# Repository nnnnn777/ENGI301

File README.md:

# EZ Cool 1.0

This device was created to automate a Lasko brand box fan, or other similar box fans, by using the PocketBeagle.

## Table of Contents

- [Features](#features)
- [Set Up](#setup)
- [Usage](#usage)

## Features

This device features LEDs, buttons, and a servo motor. Bluetooth integration will be added in the future.

## Set Up
Instructions on device build and set up can be found at the following Hackster page: [Hackster](https://www.hackster.io/511889/ez-cool-1-0-pocketbeagle-5790c5)

## Usage

This device operates on its own once connected to power. Simply plug in EZ Cool 1.0 after attaching to the fan and wait for the red LED to power on.

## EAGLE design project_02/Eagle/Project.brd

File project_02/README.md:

# ENGI 301: Project 2/EZ Cool

This folder contains files pertaining to the electronic components of the EZ Cool PocketBeagle based device by Nate Miller including .sch, .brd, .lib, and some other miscellaneous files.
For more on this device, please see project_1.

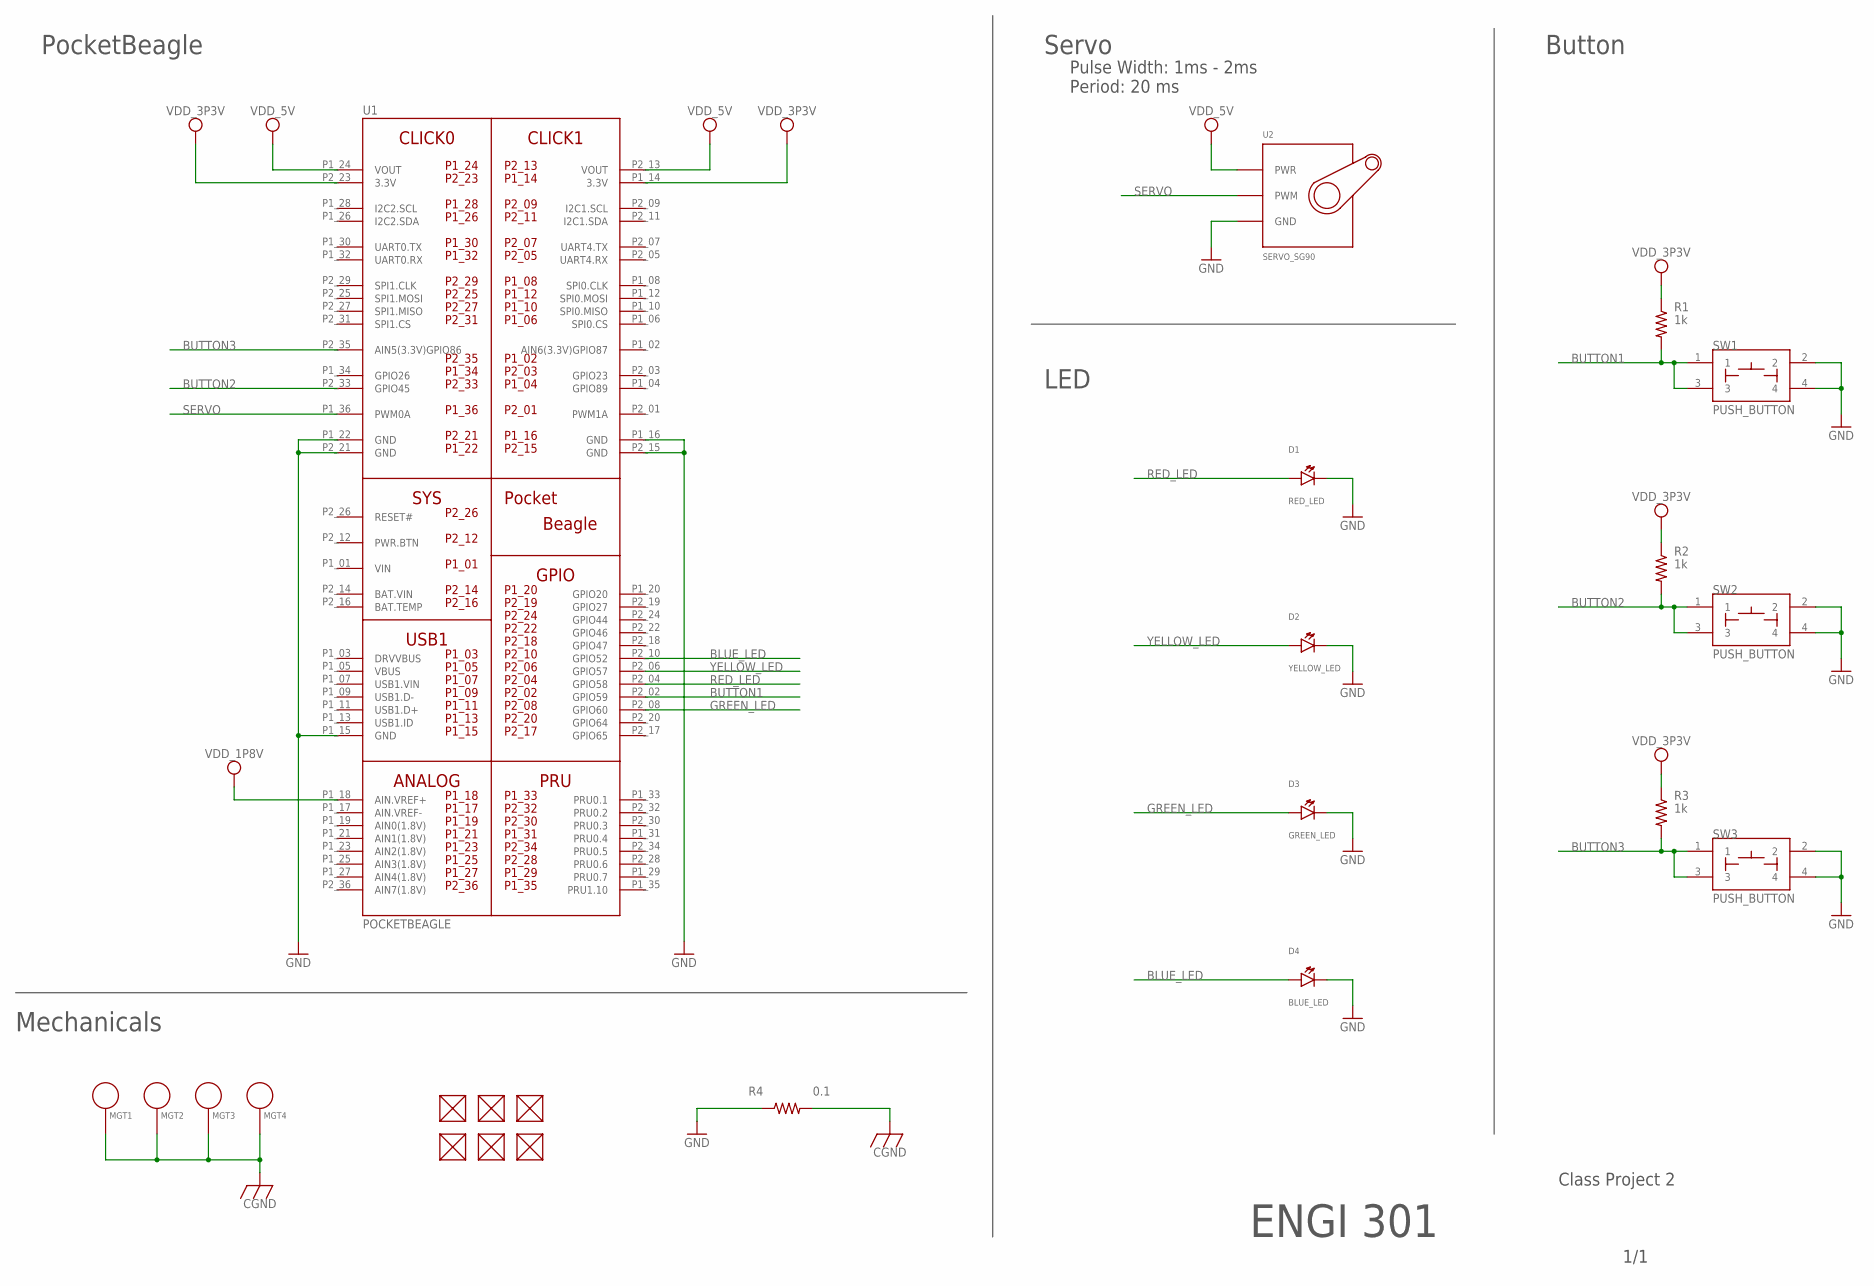
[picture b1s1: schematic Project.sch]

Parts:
D1: RED_LED; EIA-STD
D2: YELLOW_LED; EIA-STD
D3: GREEN_LED; EIA-STD
D4: BLUE_LED; EIA-STD
FUD1, FUD2, FUD3, FUD4, FUD5, FUD6: FIDUCIAL; FIDUCIAL_40MIL
MGT1, MGT2, MGT3, MGT4: MOUNTING_HOLE
R1, R2, R3: 1k; R0603
R4: 0.1; R0805
SW1, SW2, SW3: PUSH_BUTTON; BUTTON_12.5MM
U1: POCKETBEAGLE
U2: SERVO_SG90; SERVO-X1

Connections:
BAT.VIN: U1.P2_14 (BAT.VIN)
BLUE_LED: D4.ANODE, U1.P2_10 (GPIO52)
BUTTON1: R1.2, SW1.1, SW1.3, U1.P2_02 (GPIO59)
BUTTON2: R2.2, SW2.1, SW2.3, U1.P2_33 (GPIO45)
BUTTON3: R3.2, SW3.1, SW3.3, U1.P2_35 (AIN5(3.3V)GPIO86)
CGND: MGT1.P$1, MGT2.P$1, MGT3.P$1, MGT4.P$1, R4.2
GND: D1.CATHODE, D2.CATHODE, D3.CATHODE, D4.CATHODE, R4.1, SW1.2, SW1.4, SW2.2, SW2.4, SW3.2, SW3.4, U1.P1_15 (GND), U1.P1_16 (GND), U1.P1_22 (GND), U1.P2_15 (GND), U1.P2_21 (GND), U2.GND
GREEN_LED: D3.ANODE, U1.P2_08 (GPIO60)
RED_LED: D1.ANODE, U1.P2_04 (GPIO58)
SERVO: U1.P1_36 (PWM0A), U2.SIG (PWM)
VDD_1P8V: U1.P1_18 (AIN.VREF+)
VDD_3P3V: R1.1, R2.1, R3.1, U1.P1_14 (3.3V), U1.P2_23 (3.3V)
VDD_5V: U1.P1_24 (VOUT), U1.P2_13 (VOUT), U2.PWR
VIN: U1.P1_01 (VIN)
YELLOW_LED: D2.ANODE, U1.P2_06 (GPIO57)

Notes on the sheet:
PocketBeagle
Servo
Button
LED
Pulse Width: 1ms - 2ms Period: 20 ms
Mechanicals
Class Project 2
1/1
ENGI 301

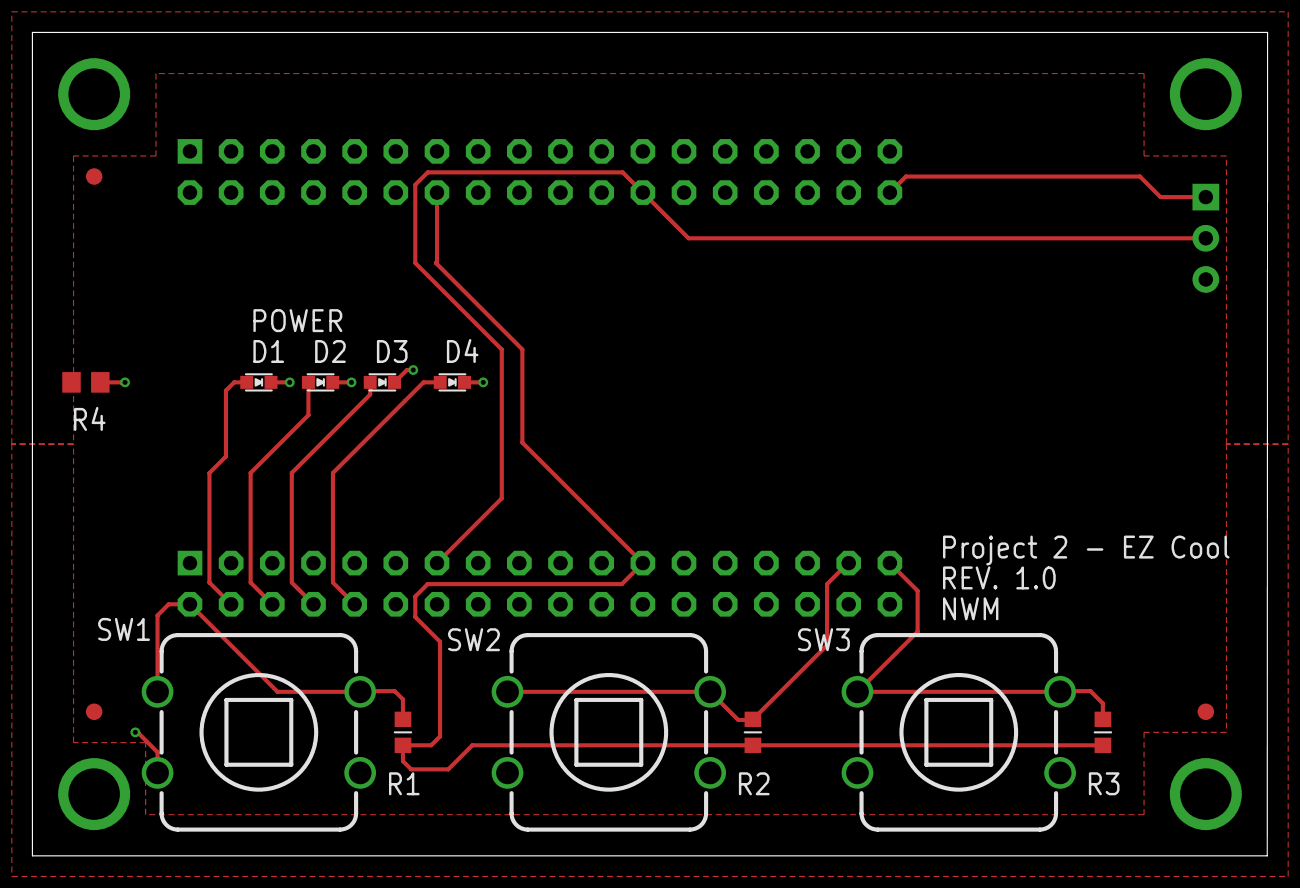
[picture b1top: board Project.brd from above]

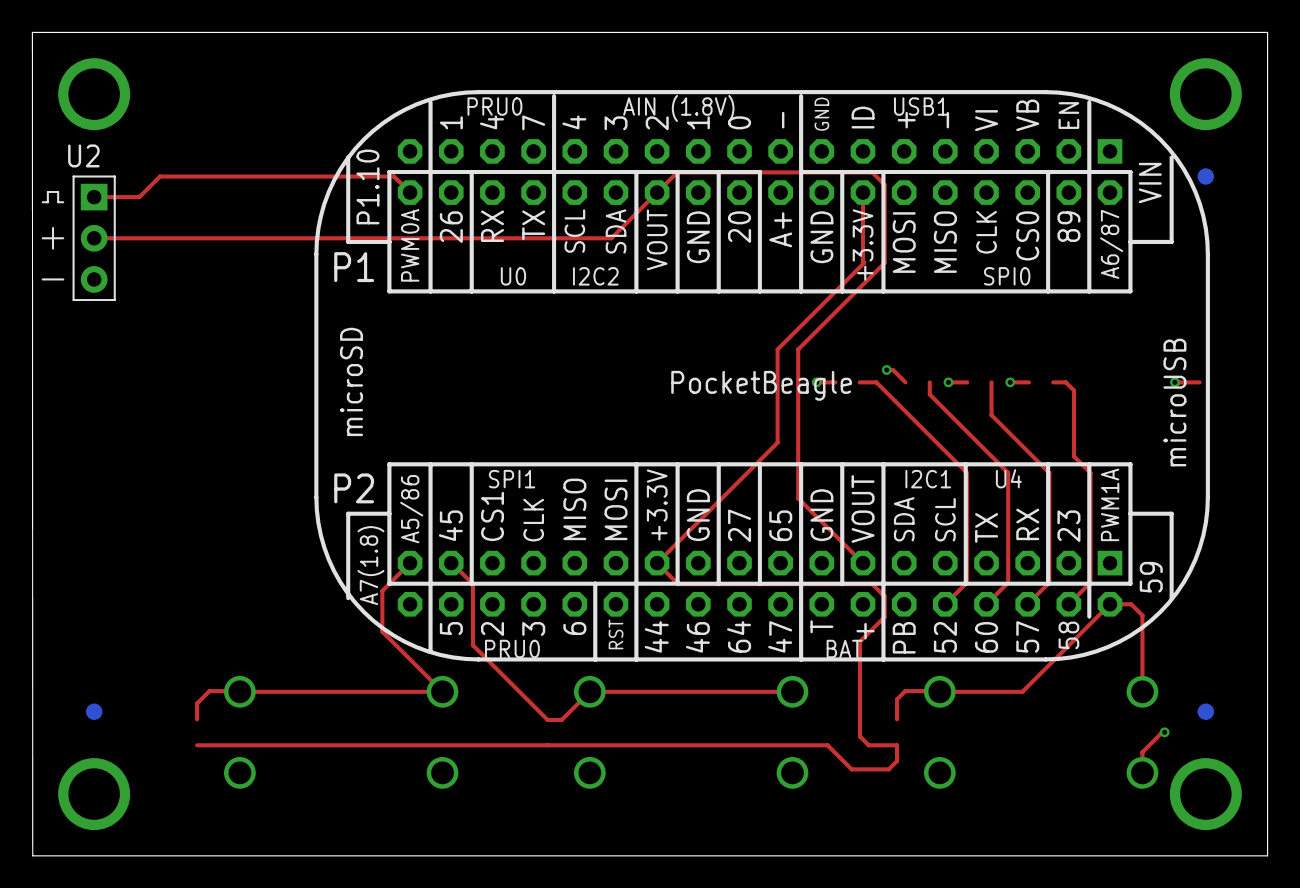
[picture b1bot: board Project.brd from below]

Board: 4 copper layers, 76.2 x 50.8 mm, 23 parts (5 on the bottom side), 12 nets.

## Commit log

2023-09-13 Updating README.md
2023-09-26 Create project_01
2023-09-27 adding project proposal
2023-09-27 homework 4 problem 3
2023-09-28 init
2023-09-28 adding blinker for problem 2 homework 4
2023-09-28 adding problem 1 for homework 4
2023-10-02 updated project proposal added
2023-10-13 adding new version of powerpoint with additonal system diagram
2023-11-19 EZ Cool 1.0
    Added Project (EZ Cool 1.0) code to git
2023-11-19 updated readme for EZ Cool Project
2023-11-19 updating readme again with hackster link
2023-12-13 project 2 stuff
    pushing project 2 things
2023-12-17 adding Project 2 Schematic/Board/Library
2023-12-17 add Project 2 BOM
2023-12-17 add Project Assembly top/bottom
2023-12-17 add all MFG files
2023-12-17 Rename project_02/Project.brd to project_02/Eagle/Project.brd
2023-12-17 Rename project_02/Project.sch to project_02/Eagle/Project.sch
2023-12-17 Rename project_02/Project_assembly.pdf to project_02/docs/Project_assembly.pdf
2023-12-17 Rename project_02/Project_assembly_bottom.pdf to project_02/docs/Project_assembly_bottom.pdf
2023-12-17 Rename project_02/Project.lbr to project_02/Eagle/Project.lbr
